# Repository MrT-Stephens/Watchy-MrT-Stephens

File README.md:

<h1 align="center">
  <br>
  MrT Stephens's Watchy GitHub Repo
  <br>
</h1>

<h4 align="center">This is my version of the Watchy E-Paper smartwatch by <a href="https://watchy.sqfmi.com" target="_blank">sqfmi</a>!</h4>

<p align="center">
  <a href="#watchy-esp32-s3">Watchy Esp32-S3</a> •
  <a href="#watchy-esp32-s3-specifications">Watchy Esp32-S3 specifications</a> •
   <a href="#watchy-esp32-s3-3d-models">Watchy Esp32-S3 3D-Models</a>
</p>

## Watchy Esp32-S3
***Current Version = V1.2***
> **Note**
> The version 1.2 has not been tested yet, as version 1.1 was having issues with the I2C bus.

## Watchy Esp32-S3 specifications
* MCU, ESP32-S3R8, Dual Core, 8MB Psram.
* Flash, 128Mbit, 16MB, W25Q128JVPIQ.
* Sensors.
   - BME688, Environmental Gas sensor.
   - BMP390, Pressure sensor.
   - BMA400, Accelerometer.
   - BMM150, Magnometer.
   - SHT41A, Temprature sensor.
   - DS3231MZ, Real Time clock.
* E-Paper Display, GDEH0154D67.
* Type C Port, USB4110-GF-A_REVB.
* PCB Antenna, swra117d.
* Tactical Buttons, K2-1114SA-A4SW-06.
* Vibration Motor.

## Watchy Esp32-S3 3D-Models

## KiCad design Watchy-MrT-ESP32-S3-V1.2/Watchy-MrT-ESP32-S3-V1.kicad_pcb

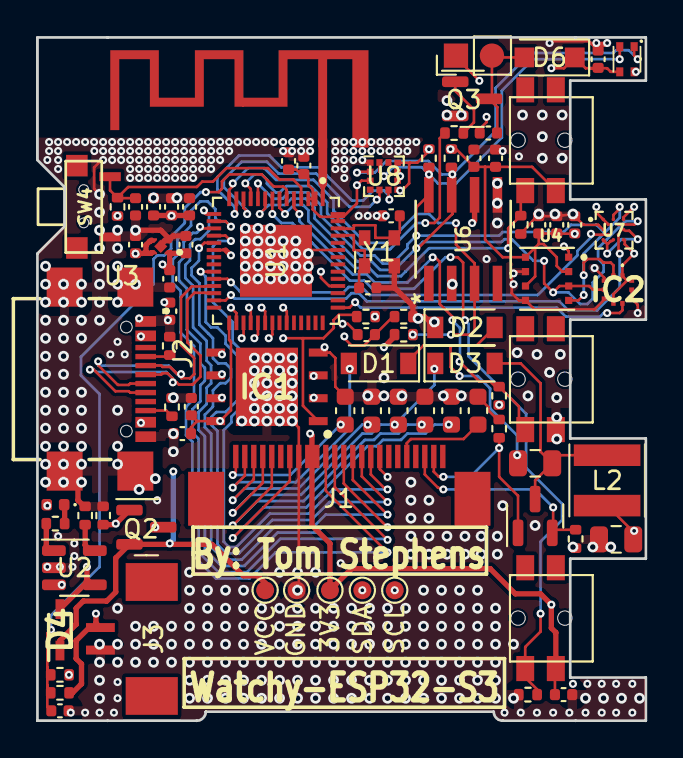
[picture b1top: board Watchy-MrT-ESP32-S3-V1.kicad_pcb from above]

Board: 4 copper layers, 33.8 x 38.0 mm, 86 parts (0 on the bottom side), 56 nets.

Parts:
3V3: TestPoint; TestPoint_Pad_D1.0mm
AE1: Device_Antenna_Chip; SWRA117D
C1, C2: 15pF; C_0402_1005Metric
C3, C5, C6, C21, C22, C31, C34: 1uF; C_0402_1005Metric
C4, C17, C19, C25, C26, C27, C28, C29, C30: 100nF; C_0402_1005Metric
C7, C33: 0.1uF; C_0402_1005Metric
C8, C9: 4.7uF/50V; C_0805_2012Metric
C10, C12, C13, C14, C15, C16: 1uF/50V; C_0603_1608Metric
C11: 1uF/50V; C_0402_1005Metric
C18, C32: 10nF; C_0402_1005Metric
C35: 2.2nF; C_0402_1005Metric
D1, D2, D3: MBR0530; D_SOD-123
D4: BAT60B; SOD2512X115N
D5: LED; LED_0402_1005Metric
D6: 1N4001; D_SOD-123F
GND: TestPoint; TestPoint_Pad_D1.0mm
IC1: W25Q128JVPIQ; SON127P600X500X80-9N-D
IC2: BMP390
J1: FPC24(0.5MM); 24_Pins_0.5mm_Pitch_ZIF_Connector_UP
J2: USB4110-GF-A_REVB; GCT_USB4110-GF-A_REVB
J3: Battery; 1.25T-2PWT (Molex 532610271)
L2: 10uH 1A; L_Taiyo-Yuden_NR-40xx
M1: Vibration_Motor; Motor_Header
Q1: AO3400A; SOT-23
Q2: CJ2301; SOT-23
Q3: S8050; SOT-23
R1, R4: 100k; R_0402_1005Metric
R2: 442k; R_0402_1005Metric
R3, R14, R15, R16, R17: 10K; R_0402_1005Metric
R5: 3; R_0402_1005Metric
R6, R7: 10k; R_0402_1005Metric
R8: 1k; R_0402_1005Metric
R9, R10: 1M; R_0402_1005Metric
R11: 1K; R_0402_1005Metric
R12, R13: 5.1k; R_0402_1005Metric
R18, R19: 4.7k; R_0402_1005Metric
SCL: TestPoint; TestPoint_Pad_D1.0mm
SDA: TestPoint; TestPoint_Pad_D1.0mm
SW1, SW2, SW3: BTN; K2-1114SA-A4SW-06
SW4: SW_Push; button_side_smd
U1: ESP32-S3; QFN40P700X700X90-57N
U2: TP4054; SOT-23-5
U3: NCP167BMX330TBG; REG_NCP167BMX330TBG
U4: BME688; IC_BME688
U6: DS3231MZ; 21-0041B_8
U7: BMM150; XDCR_BMM150
U8: BMA400; LGA-12_2x2mm_P0.5mm
U9: SHT4XA
VCC: TestPoint; TestPoint_Pad_D1.0mm
Y1: 40 MHz; Oscillator_SMD_Abracon_ASDMB-4Pin_2.5x2.0mm

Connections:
+3V3: 3V3.1, C4.1, C8.1, C11.1, C17.1, C19.1, C22.2, C25.1, C26.1, C27.1, C28.1, C29.1, C30.1, C31.1, C32.1, C33.1, C34.1, C35.1, D6.1 (K), IC2.1 (VDDIO), IC2.6 (CSB), IC2.10 (VDD), J1.15, J1.16, L2.2, M1.1 (+), R1.1, R15.1, R18.1, R19.1, SW1.1, SW3.1, U1.2 (VDD3P3), U1.3 (VDD3P3), U1.20 (VDD3P3_RTC), U1.46 (VDD3P3_CPU), U1.55 (VDDA1), U1.56 (VDDA2), U3.1 (OUT), U4.2 (CSB), U4.6 (VDDIO), U4.8 (VDD), U7.A1 (PS), U7.A5 (CSB), U7.B2 (VDDIO), U7.E5 (VDD), U8.3 (VDDIO), U8.7 (VDD), U8.10 (CSB), U9.3 (VDD)
+BATT: J3.1, Q2.3 (D), R9.1, R17.1, U2.3 (VBAT), U6.6 (VBAT)
/MCU_Sheet/CHIP_PU: C3.2, R1.2, SW4.2, U1.4 (CHIP_PU)
/MCU_Sheet/GDR: J1.2, Q1.1 (G), R3.1
/MCU_Sheet/LNA_IN: AE1.1 (FEED), U1.1 (LNA_IN)
/MCU_Sheet/PREVGH: C10.1, D3.1 (K), J1.21
/MCU_Sheet/PREVGL: D1.2 (A), J1.23
/MCU_Sheet/RESE: J1.3, Q1.2 (S), R5.2
/MCU_Sheet/SPICLK: IC1.6 (CLK), U1.33 (SPICLK)
/MCU_Sheet/SPICLK_P: C5.1, R2.1, U1.37 (SPICLK_P)
/MCU_Sheet/SPICS0: IC1.1 (~CS), R4.2, U1.32 (SPICS0)
/MCU_Sheet/SPID: IC1.5 (DI_(IO0)), U1.35 (SPID)
/MCU_Sheet/SPIHD: IC1.7 (~HOLD_OR_/RESET_(IO3)), U1.30 (SPIHD)
/MCU_Sheet/SPIQ: IC1.2 (DO_(IO1)), U1.34 (SPIQ)
/MCU_Sheet/SPIWP: IC1.3 (~WP_(IO2)), U1.31 (SPIWP)
/MCU_Sheet/XTAL_N: C2.2, U1.53 (XTAL_N), Y1.1
/MCU_Sheet/XTAL_P: C1.2, U1.54 (XTAL_P), Y1.3
/Power_Managment_Sheet/CC1: J2.A5 (CC1), R12.1
/Power_Managment_Sheet/CC2: J2.B5 (CC2), R13.1
ACCEL_INT1: U1.12 (GPIO7), U8.5 (INT1)
ACCEL_INT2: U1.13 (GPIO8), U8.6 (INT2)
BAT_ADC: C18.1, R9.2, R10.1, U1.6 (GPIO1)
BMP_INT: IC2.7 (INT), U1.43 (GPIO38)
BTN1: R14.2, SW1.2, U1.7 (GPIO2)
BTN2: R15.2, SW2.2, U1.5 (GPIO0)
BTN3: R16.2, SW3.2, U1.8 (GPIO3)
D_BUSY: J1.9, U1.18 (GPIO13)
D_DC: J1.11, U1.19 (GPIO14)
D_MOSI: J1.14, U1.16 (GPIO11)
D_RES: J1.10, U1.23 (GPIO17)
D_SCK: J1.13, U1.17 (GPIO12)
D_SS: J1.12, U1.15 (GPIO10)
GND: AE1.2 (PCB_Trace), C1.1, C2.1, C3.1, C4.2, C5.2, C6.2, C7.2, C8.2, C10.2, C11.2, C12.2, C13.2, C14.2, C15.2, C16.2, C17.2, C18.2, C21.1, C22.1, C25.2, C26.2, C27.2, C28.2, C29.2, C30.2, C31.2, C32.2, C33.2, C34.2, C35.2, D2.1 (K), GND.1, IC1.4 (GND_1), IC1.9 (GND_2), IC2.3 (VSS_1), IC2.5 (SDO), IC2.8 (VSS_2), IC2.9 (VSS_3), J1.8, J1.17, J2.A1/B12 (GND), J2.B1/A12 (GND), J2.S1 (GND), J2.S2 (GND), J2.S3 (GND), J2.S4 (GND), J3.2, Q3.2 (E), R2.2, R3.2, R5.1, R6.2, R7.2, R10.2, R12.2, R13.2, R14.1, R16.1, SW2.1, SW4.1, U1.51 (GPIO45), U1.57 (GND), U2.2 (VSS), U3.2 (GND), U3.5 (EXP), U4.1 (GND), U4.5 (SDO), U4.7 (GND), U6.2 (VCC), U6.5 (GND), U7.C1 (SDO), U7.C5 (GND), U7.E1 (GND), U7.E3 (GND), U8.1 (SDO), U8.8 (GNDIO), U8.9 (GND), U9.4 (VSS), Y1.2
I2C_SCL: IC2.2 (SCK), R19.2, SCL.1, U1.10 (GPIO5), U4.4 (SCK), U6.8 (SCL), U7.A3 (SCK), U8.12 (SCX), U9.2 (SCL/T)
I2C_SDA: IC2.4 (SDI), R18.2, SDA.1, U1.9 (GPIO4), U4.3 (SDI), U6.7 (SDA), U7.B4 (SDI), U8.2 (SDX), U9.1 (SDA/RH)
MAG_DRDY: U1.27 (GPIO21), U7.D4 (DRDY)
MAG_INT: U1.24 (GPIO18), U7.D2 (INT)
unnamed: C9.1, D1.1 (K), D2.2 (A)
unnamed: C9.2, D3.2 (A), L2.1, Q1.3 (D)
unnamed: D5.1 (K), R8.1
unnamed: C19.2, D6.2 (A), M1.2 (-), Q3.3 (C)
unnamed: C12.1, J1.5
unnamed: C13.1, J1.18
unnamed: C14.1, J1.20
unnamed: C15.1, J1.22
unnamed: C16.1, J1.24
unnamed: Q3.1 (B), R11.1
unnamed: R7.1, U2.5 (PROG)
unnamed: R8.2, U2.1 (STAT)
RTC_INT: R17.2, U1.14 (GPIO9), U6.3 (~INT/SQW)
USB_N: J2.A7 (DN1), J2.B7 (DN2), U1.25 (GPIO19)
USB_P: J2.A6 (DP1), J2.B6 (DP2), U1.26 (GPIO20)
VBUS: D4.2, D5.2 (A), J2.A4/B9 (VBUS), J2.B4/A9 (VBUS), Q2.1 (G), R6.1, U2.4 (VDD)
VCC: C21.2, D4.1, Q2.2 (S), U3.3 (EN), U3.4 (IN), VCC.1
VDD_SPI: C6.1, C7.1, IC1.8 (VCC), R4.1, U1.29 (VDD_SPI)
VIB_PWM: R11.2, U1.11 (GPIO6)

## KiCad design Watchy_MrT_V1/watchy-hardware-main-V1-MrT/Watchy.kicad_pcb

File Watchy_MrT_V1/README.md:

<h1>Watchy V1! By: MrT Stephens</h1>
<h2>Pictures:</h2>
PCB 3D View image:
<p>
  [image](https://user-images.githubusercontent.com/92452307/159169245-4fe227ef-48c2-4300-9ce5-b4dbfc84516c.png?raw=true)
<p>Soldered PCB image:
<p>
<p>Screen image:
<p>

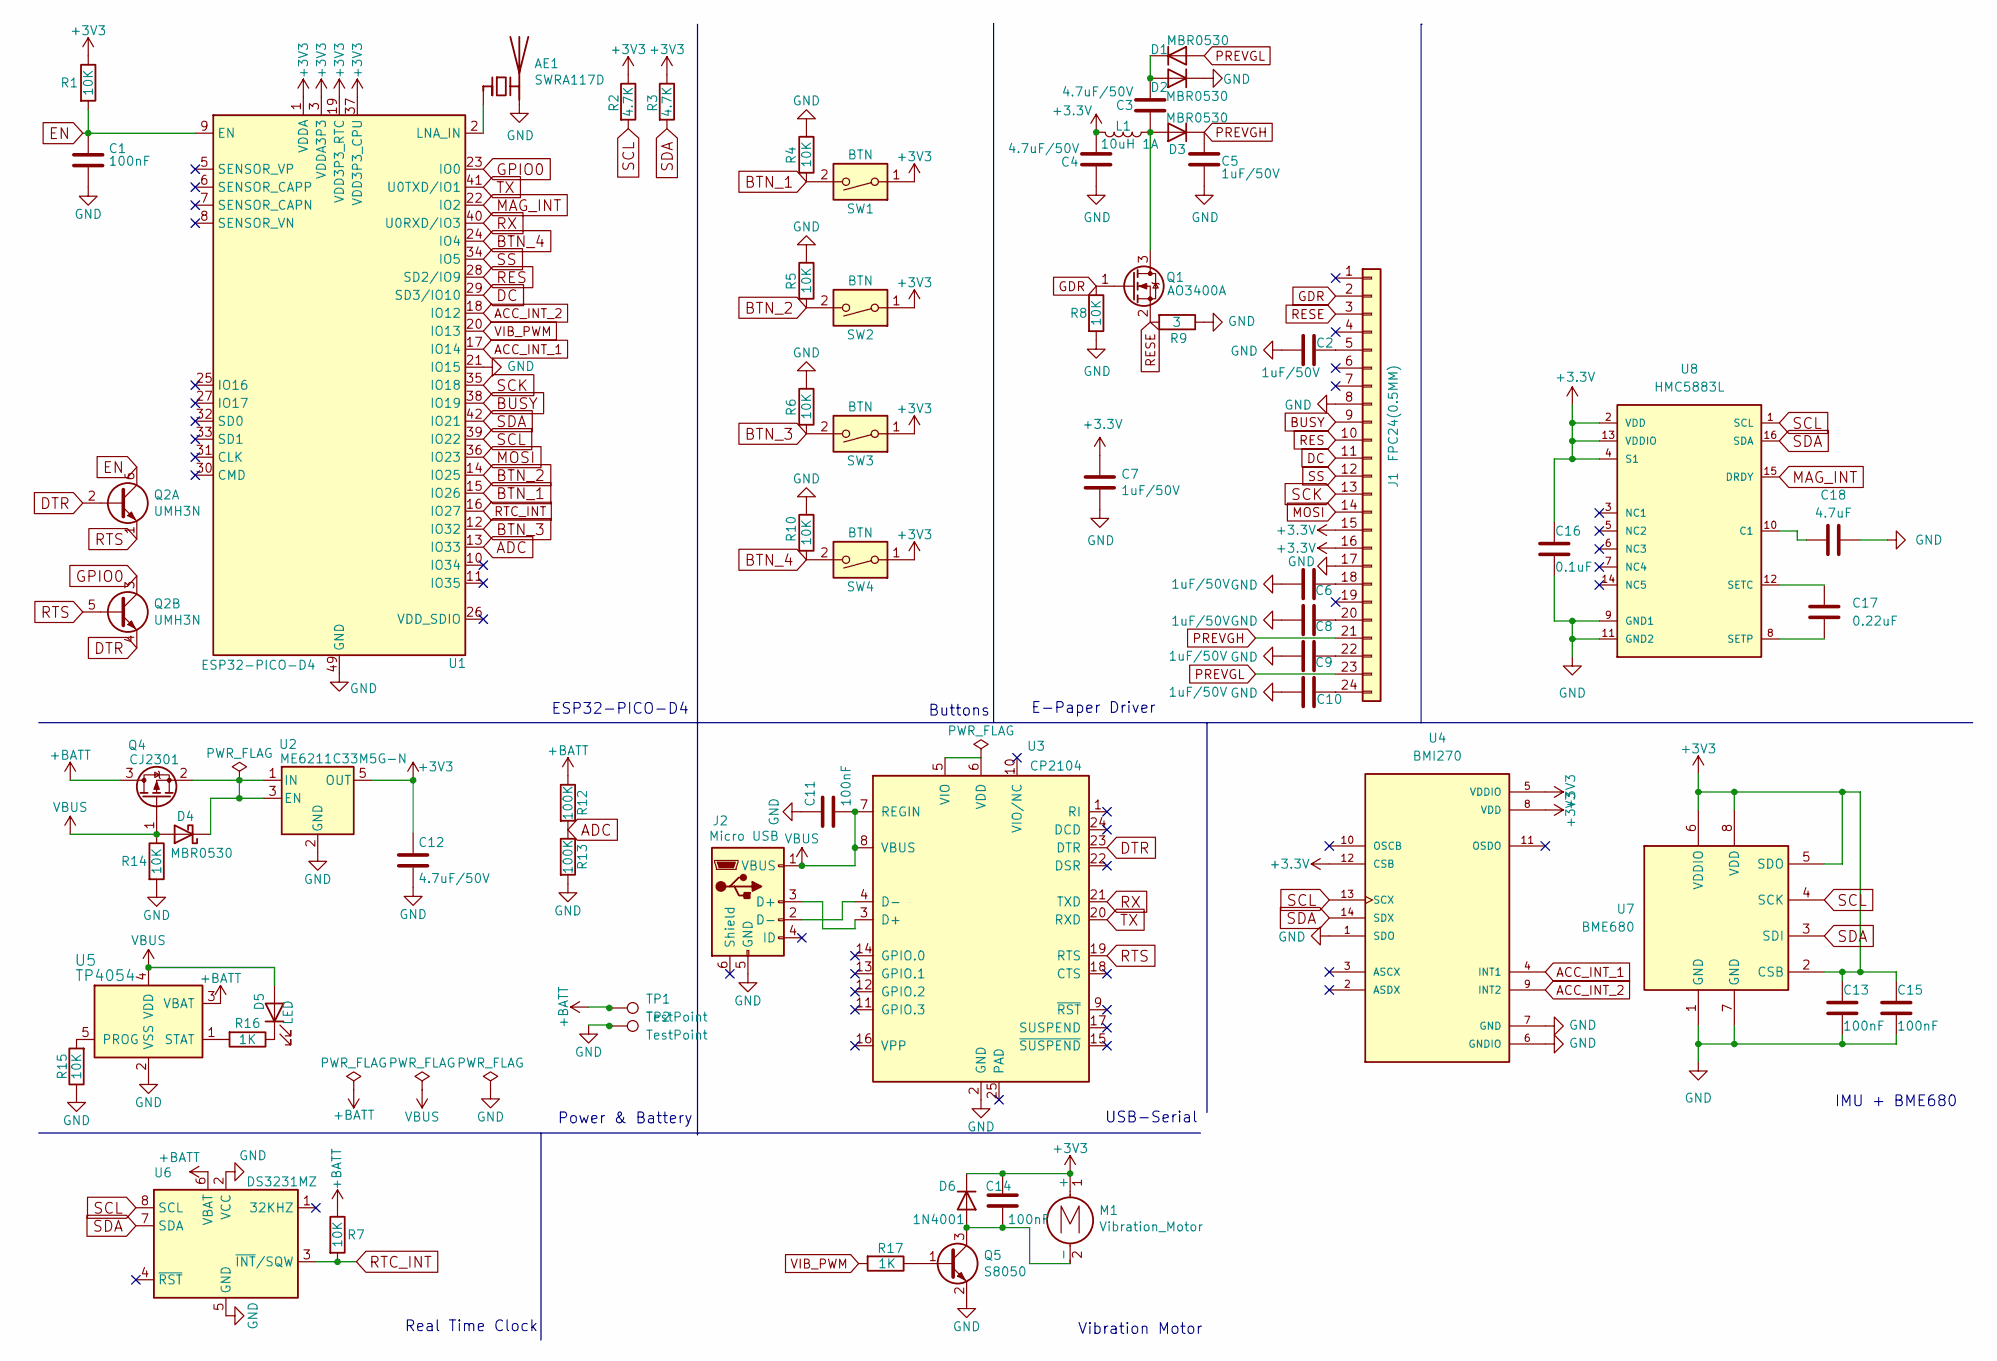
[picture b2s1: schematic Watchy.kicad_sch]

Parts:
AE1: SWRA117D
C1, C11, C13, C14, C15: 100nF; C_0603_1608Metric
C2, C5, C6, C7, C8, C9, C10: 1uF/50V; C_0603_1608Metric
C3, C4, C12: 4.7uF/50V; C_0805
C16: 0.1uF; C_0603_1608Metric
C17: 0.22uF; C_0603_1608Metric
C18: 4.7uF; C_0603_1608Metric
D1, D2, D3, D4: MBR0530; D_SOD-123
D5: LED; LED_0603
D6: 1N4001; D_SOD-123F
J1: FPC24(0.5MM); 24_Pins_0.5mm_Pitch_ZIF_Connector_UP
J2: Micro USB; USB_Micro-B
L1: 10uH 1A; Inductor_Taiyo-Yuden_NR-40xx
M1: Vibration_Motor; Motor_Header
Q1: AO3400A; SOT-23
Q2: UMH3N; SOT-363_SC-70-6
Q4: CJ2301; SOT-23
Q5: S8050; SOT-23
R1, R4, R5, R6, R7, R8, R10, R14, R15: 10K; R_0402
R2, R3: 4.7K; R_0402
R9: 3; R_0402
R12, R13: 100K; R_0402
R16, R17: 1K; R_0402
SW1, SW2, SW3, SW4: BTN; K2-1114SA-A4SW-06
TP1, TP2: TestPoint; TestPoint_Pad_2.0x2.0mm
U1: ESP32-PICO-D4; QFN-48-1EP_7x7mm_Pitch0.5mm
U2: ME6211C33M5G-N; SOT-23-5
U3: CP2104; QFN-24-1EP_4x4mm_P0.5mm_EP2.6x2.6mm
U4: BMI270; XDCR_BMI270
U5: TP4054; SOT-23-5
U6: DS3231MZ; SOIC-8_3.9x4.9mm_Pitch1.27mm
U7: BME680; Bosch_LGA-8_3x3mm_P0.8mm_ClockwisePinNumbering
U8: HMC5883L

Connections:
+BATT: Q4.3 (D), R7.1, R12.1, TP1.1, U5.3 (VBAT), U6.6 (VBAT); also elsewhere on the board
ACC_INT_1: U1.17 (IO14), U4.4 (INT1)
ACC_INT_2: U1.18 (IO12), U4.9 (INT2)
ADC: R12.2, R13.1, U1.13 (IO33)
BTN_1: R4.2, SW1.2, U1.15 (IO26)
BTN_2: R5.2, SW2.2, U1.14 (IO25)
BTN_3: R6.2, SW3.2, U1.12 (IO32)
BTN_4: R10.2, SW4.2, U1.24 (IO4)
BUSY: J1.9, U1.38 (IO19)
DC: J1.11, U1.29 (SD3/IO10)
DTR: Q2.2 (B1), Q2.4 (E2), U3.23 (DTR)
EN: C1.1, Q2.6 (C1), R1.2, U1.9 (EN)
GDR: J1.2, Q1.1 (G), R8.1
GND: AE1.2 (PCB_Trace), C1.2, C2.2, C4.2, C5.2, C6.2, C7.2, C8.2, C9.2, C10.2, C11.1, C12.2, C13.2, C15.2, C16.2, C18.2, D2.1 (K), J1.8, J1.17, J2.5 (GND), Q5.2 (E), R4.1, R5.1, R6.1, R8.2, R9.1, R10.1, R13.2, R14.2, R15.1, TP2.1, U1.21 (IO15), U1.49 (GND), U2.2 (GND), U3.2 (GND), U4.1 (SDO), U4.6 (GNDIO), U4.7 (GND), U5.2 (VSS), U6.2 (VCC), U6.5 (GND), U7.1 (GND), U7.7 (GND), U8.9 (GND1), U8.11 (GND2); also elsewhere on the board
GPIO0: Q2.3 (C2), U1.23 (IO0)
MAG_INT: U1.22 (IO2), U8.15 (DRDY)
MOSI: J1.14, U1.36 (IO23)
unnamed: AE1.1 (FEED), U1.2 (LNA_IN)
unnamed: C3.1, D1.1 (K), D2.2 (A)
unnamed: C3.2, D3.2 (A), L1.1, Q1.3 (D)
unnamed: D4.1 (K), Q4.2 (S), U2.1 (IN), U2.3 (EN)
unnamed: D5.1 (K), R16.1
unnamed: C14.2, D6.2 (A), M1.2 (-), Q5.3 (C)
unnamed: C2.1, J1.5
unnamed: C6.1, J1.18
unnamed: C8.1, J1.20
unnamed: C9.1, J1.22
unnamed: C10.1, J1.24
unnamed: J2.3 (D+), U3.3 (D+)
unnamed: J2.2 (D-), U3.4 (D-)
unnamed: Q5.1 (B), R17.1
unnamed: U3.5 (VIO), U3.6 (VDD)
unnamed: R15.2, U5.5 (PROG)
unnamed: R16.2, U5.1 (STAT)
unnamed: C18.1, U8.10 (C1)
unnamed: C17.1, U8.12 (SETC)
unnamed: C17.2, U8.8 (SETP)
PREVGH: C5.1, D3.1 (K), J1.21
PREVGL: D1.2 (A), J1.23
RES: J1.10, U1.28 (SD2/IO9)
RESE: J1.3, Q1.2 (S), R9.2
RTC_INT: R7.2, U1.16 (IO27), U6.3 (~INT/SQW)
RTS: Q2.1 (E1), Q2.5 (B2), U3.19 (RTS)
RX: U1.40 (U0RXD/IO3), U3.21 (TXD)
SCK: J1.13, U1.35 (IO18)
SCL: R2.2, U1.39 (IO22), U4.13 (SCX), U6.8 (SCL), U7.4 (SCK), U8.1 (SCL)
SDA: R3.2, U1.42 (IO21), U4.14 (SDX), U6.7 (SDA), U7.3 (SDI), U8.16 (SDA)
SS: J1.12, U1.34 (IO5)
TX: U1.41 (U0TXD/IO1), U3.20 (RXD)
VBUS: C11.2, D4.2 (A), D5.2 (A), J2.1 (VBUS), Q4.1 (G), R14.1, U3.7 (REGIN), U3.8 (VBUS), U5.4 (VDD)
VIB_PWM: R17.2, U1.20 (IO13)

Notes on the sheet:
Buttons
Vibration Motor
ESP32-PICO-D4
IMU + BME680
USB-Serial
Power & Battery
Real Time Clock
E-Paper Driver

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
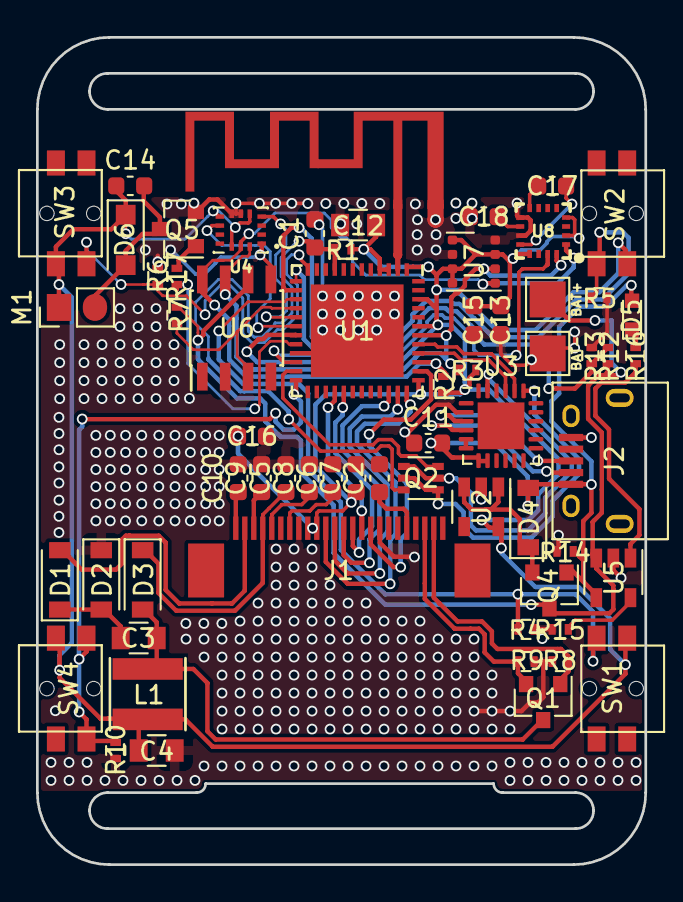
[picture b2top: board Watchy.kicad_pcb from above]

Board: 2 copper layers, 33.8 x 46.0 mm, 63 parts (0 on the bottom side), 52 nets.

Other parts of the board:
BAT+: TestPoint; TestPoint_Pad_2.0x2.0mm
BAT-: TestPoint; TestPoint_Pad_2.0x2.0mm

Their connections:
+BATT: BAT+.1; also elsewhere on the board
GND: BAT-.1; also elsewhere on the board

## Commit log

2022-03-20 Rename Readme.md to README.md
2022-03-20 This is version 1 of my custom Watchy.
2022-10-19 Watchy-MrT-ESP32-S3
2022-12-11 Watchy-ESP32-S3-V1.2
2022-12-11 Added images
2022-12-12 Added new 3d-models
2022-12-12 Added 3d-models
